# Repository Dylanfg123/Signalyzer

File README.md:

View this project on [CADLAB.io](https://cadlab.io/project/26944). 

# Signalyzer

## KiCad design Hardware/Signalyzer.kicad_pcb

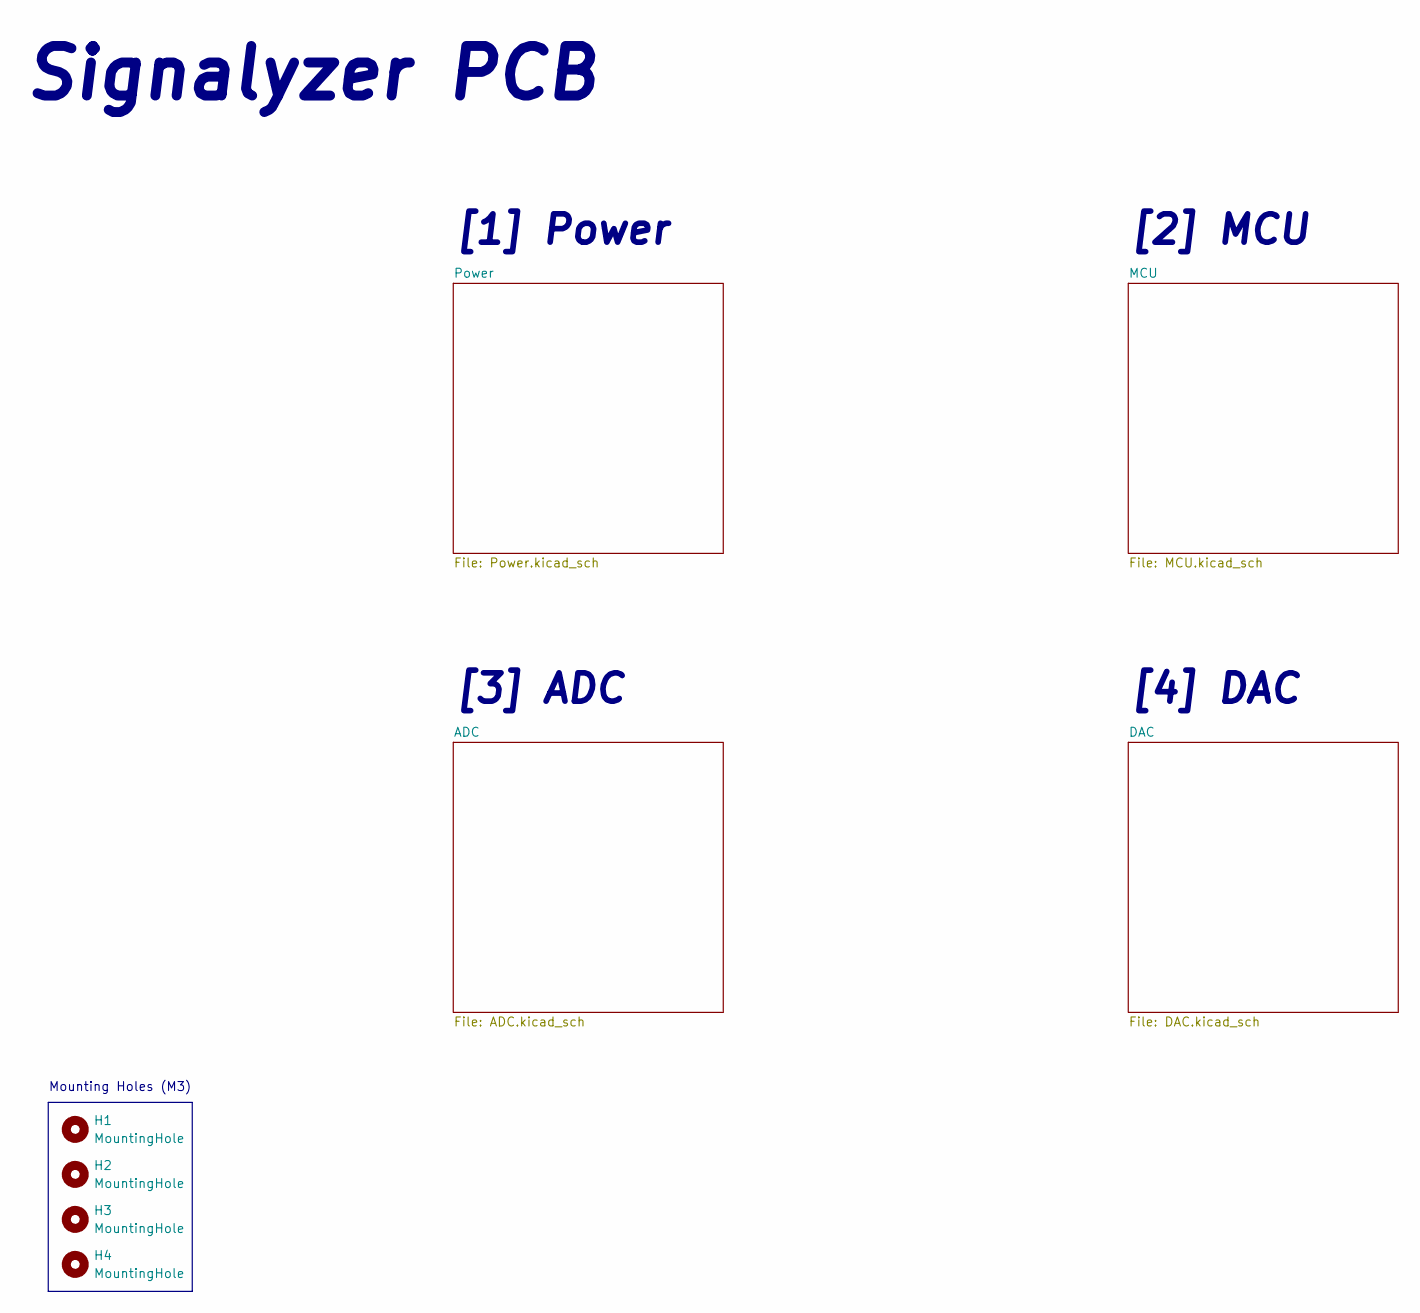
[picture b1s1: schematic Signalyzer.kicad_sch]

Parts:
H1, H2, H3, H4: MountingHole; MountingHole_3.2mm_M3

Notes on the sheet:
[2] MCU
Mounting Holes (M3)
[4] DAC
Signalyzer PCB
[3] ADC
[1] Power

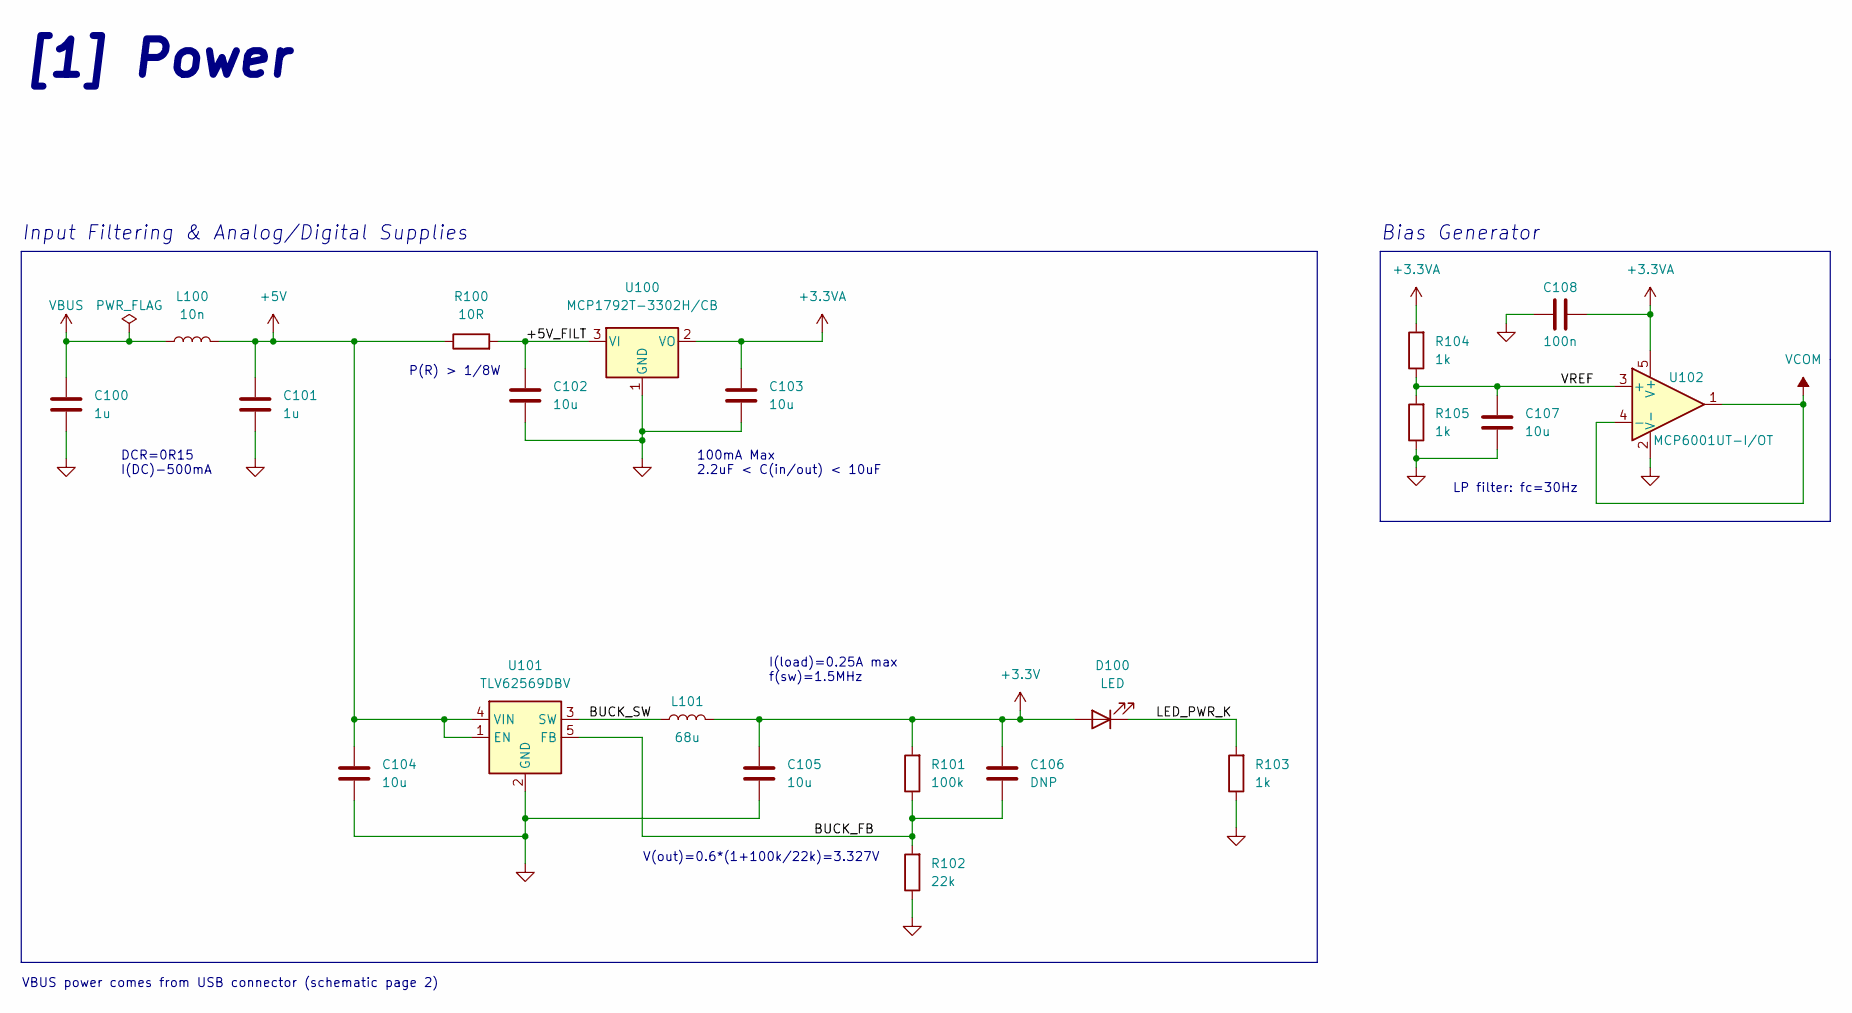
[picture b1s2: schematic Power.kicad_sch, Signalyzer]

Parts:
C100, C101: 1u; C_0603_1608Metric; Manufacturer Part Number CL10B105KA8VPJC; LCSC Part # C472462
C102, C103, C104, C105, C107: 10u; C_0603_1608Metric; Manufacturer Part Number GRM188R61C106KAALD; LCSC Part # C86275
C106: DNP; C_0402_1005Metric
C108: 100n; C_0402_1005Metric; Manufacturer Part Number CGA2B3X7R1V104KT0Y0F; LCSC Part # C343047
D100: LED; LED_0603_1608Metric; Manufacturer Part Number TJ-S1608SW6TDSLC2R2G-A5; LCSC Part # C601671
L100: 10n; L_0402_1005Metric; Manufacturer Part Number MHQ1005P10NJT000; LCSC Part # C445746
L101: 68u; L_1210_3225Metric; Manufacturer Part Number BCL322520RT-680M-D; LCSC Part # C3221319
R100: 10R; R_0805_2012Metric; Manufacturer Part Number RTAN0805BKE10R0; LCSC Part # C346749
R101: 100k; R_0402_1005Metric; Manufacturer Part Number ERA2AEB104X; LCSC Part # C445619
R102: 22k; R_0402_1005Metric; Manufacturer Part Number PTFR0402B22K0N9; LCSC Part # C2693021
R103, R104, R105: 1k; R_0402_1005Metric; Manufacturer Part Number ERA2AEB102X; LCSC Part # C445596
U100: MCP1792T-3302H/CB; SOT-23; Manufacturer Part Number MCP1792T-3302H/CB
U101: TLV62569DBV; SOT-23-5; Manufacturer Part Number TLV62569DBVR
U102: MCP6001UT-I/OT; SOT-23-5; Manufacturer Part Number MCP6001UT-I/OT

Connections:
+3.3VA: C103.1, C108.2, R104.2, U100.2 (VO), U102.5 (V+); also elsewhere on the board
+3V3: C105.1, C106.1, D100.2 (A), L101.2, R101.2; also elsewhere on the board
+5V: C101.1, C104.1, L100.2, R100.1, U101.1 (EN), U101.4 (VIN); also elsewhere on the board
/Power/+5V_FILT: C102.1, R100.2, U100.3 (VI)
/Power/BUCK_FB: C106.2, R101.1, R102.2, U101.5 (FB)
/Power/BUCK_SW: L101.1, U101.3 (SW)
/Power/LED_PWR_K: D100.1 (K), R103.2
/Power/VREF: C107.1, R104.1, R105.2, U102.3 (+)
GND: C100.2, C101.2, C102.2, C103.2, C104.2, C105.2, C107.2, C108.1, R102.1, R103.1, R105.1, U100.1 (GND), U101.2 (GND), U102.2 (V-); also elsewhere on the board
VBUS: C100.1, L100.1; also elsewhere on the board
VCOM: U102.1, U102.4 (-); also elsewhere on the board

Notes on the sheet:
100mA Max 2.2uF < C(in/out) < 10uF
VBUS power comes from USB connector (schematic page 2)
P(R) > 1/8W
V(out)=0.6*(1+100k/22k)=3.327V
LP filter: fc=30Hz
I(load)=0.25A max f(sw)=1.5MHz
DCR=0R15 I(DC)-500mA
Input Filtering & Analog/Digital Supplies
Bias Generator
[1] Power

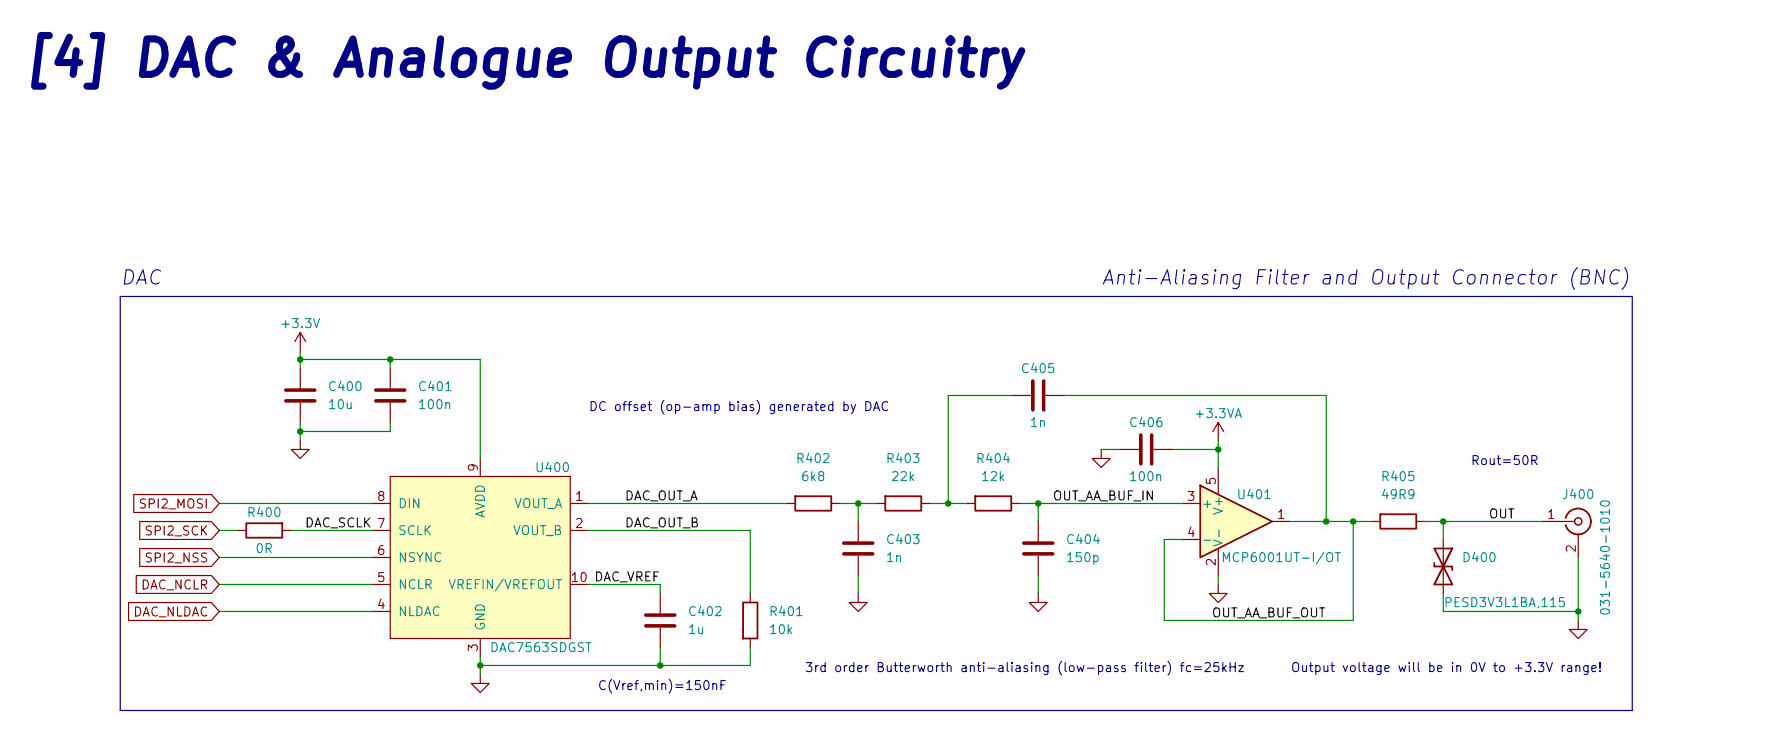
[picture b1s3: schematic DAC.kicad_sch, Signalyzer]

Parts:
C400: 10u; C_0603_1608Metric; Manufacturer Part Number GRM188R61C106KAALD; LCSC Part # C86275
C401, C406: 100n; C_0402_1005Metric; Manufacturer Part Number CGA2B3X7R1V104KT0Y0F; LCSC Part # C343047
C402: 1u; C_0603_1608Metric; Manufacturer Part Number CL10B105KA8VPJC; LCSC Part # C472462
C403, C405: 1n; C_0402_1005Metric; Manufacturer Part Number GRM1555C2A102GE01D; LCSC Part # C3010445
C404: 150p; C_0402_1005Metric; Manufacturer Part Number CC0402KRX7R9BB151; LCSC Part # C113789
D400: PESD3V3L1BA,115; D_SOD-323; Manufacturer Part Number PESD3V3L1BA,115; LCSC Part # C51450
J400: 031-5640-1010; BNC_Amphenol_B6252HB-NPP3G-50_Horizontal; Manufacturer Part Number 031-5640-1010
R400: 0R; R_0402_1005Metric; Manufacturer Part Number HCJ0402ZT0R00; LCSC Part # C346504
R401: 10k; R_0402_1005Metric; Manufacturer Part Number ERJPA2F1002X; LCSC Part # C427247
R402: 6k8; R_0402_1005Metric; Manufacturer Part Number ERA2VEB6801X; LCSC Part # C543679
R403: 22k; R_0402_1005Metric; Manufacturer Part Number PTFR0402B22K0N9; LCSC Part # C2693021
R404: 12k; R_0402_1005Metric; Manufacturer Part Number ERA2AEB123X; LCSC Part # C215763
R405: 49R9; R_0402_1005Metric; Manufacturer Part Number PTFR0402B49K9N9; LCSC Part # C2692755
U400: DAC7563SDGST; VSSOP-10; Manufacturer Part Number DAC7563SDGST
U401: MCP6001UT-I/OT; SOT-23-5; Manufacturer Part Number MCP6001UT-I/OT

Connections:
+3.3VA: C406.1, U401.5 (V+); also elsewhere on the board
+3V3: C400.1, C401.1, U400.9 (AVDD); also elsewhere on the board
/DAC/DAC_OUT_A: R402.2, U400.1 (VOUT_A)
/DAC/DAC_OUT_B: R401.1, U400.2 (VOUT_B)
/DAC/DAC_SCLK: R400.2, U400.7 (SCLK)
/DAC/DAC_VREF: C402.1, U400.10 (VREFIN/VREFOUT)
/DAC/OUT: D400.1 (A1), J400.1 (In), R405.1
/DAC/OUT_AA_BUF_IN: C404.1, R404.1, U401.3 (+)
/DAC/OUT_AA_BUF_OUT: C405.2, R405.2, U401.1, U401.4 (-)
DAC_NCLR: U400.5 (NCLR); also elsewhere on the board
DAC_NLDAC: U400.4 (NLDAC); also elsewhere on the board
GND: C400.2, C401.2, C402.2, C403.2, C404.2, C406.2, D400.2 (A2), J400.2 (Ext), R401.2, U400.3 (GND), U401.2 (V-); also elsewhere on the board
unnamed: C403.1, R402.1, R403.2
unnamed: C405.1, R403.1, R404.2
SPI2_MOSI: U400.8 (DIN); also elsewhere on the board
SPI2_NSS: U400.6 (NSYNC); also elsewhere on the board
SPI2_SCK: R400.1; also elsewhere on the board

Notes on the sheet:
Rout=50R
3rd order Butterworth anti-aliasing (low-pass filter) fc=25kHz
DAC
DC offset (op-amp bias) generated by DAC
Anti-Aliasing Filter and Output Connector (BNC)
C(Vref,min)=150nF
[4] DAC & Analogue Output Circuitry
Output voltage will be in 0V to +3.3V range!

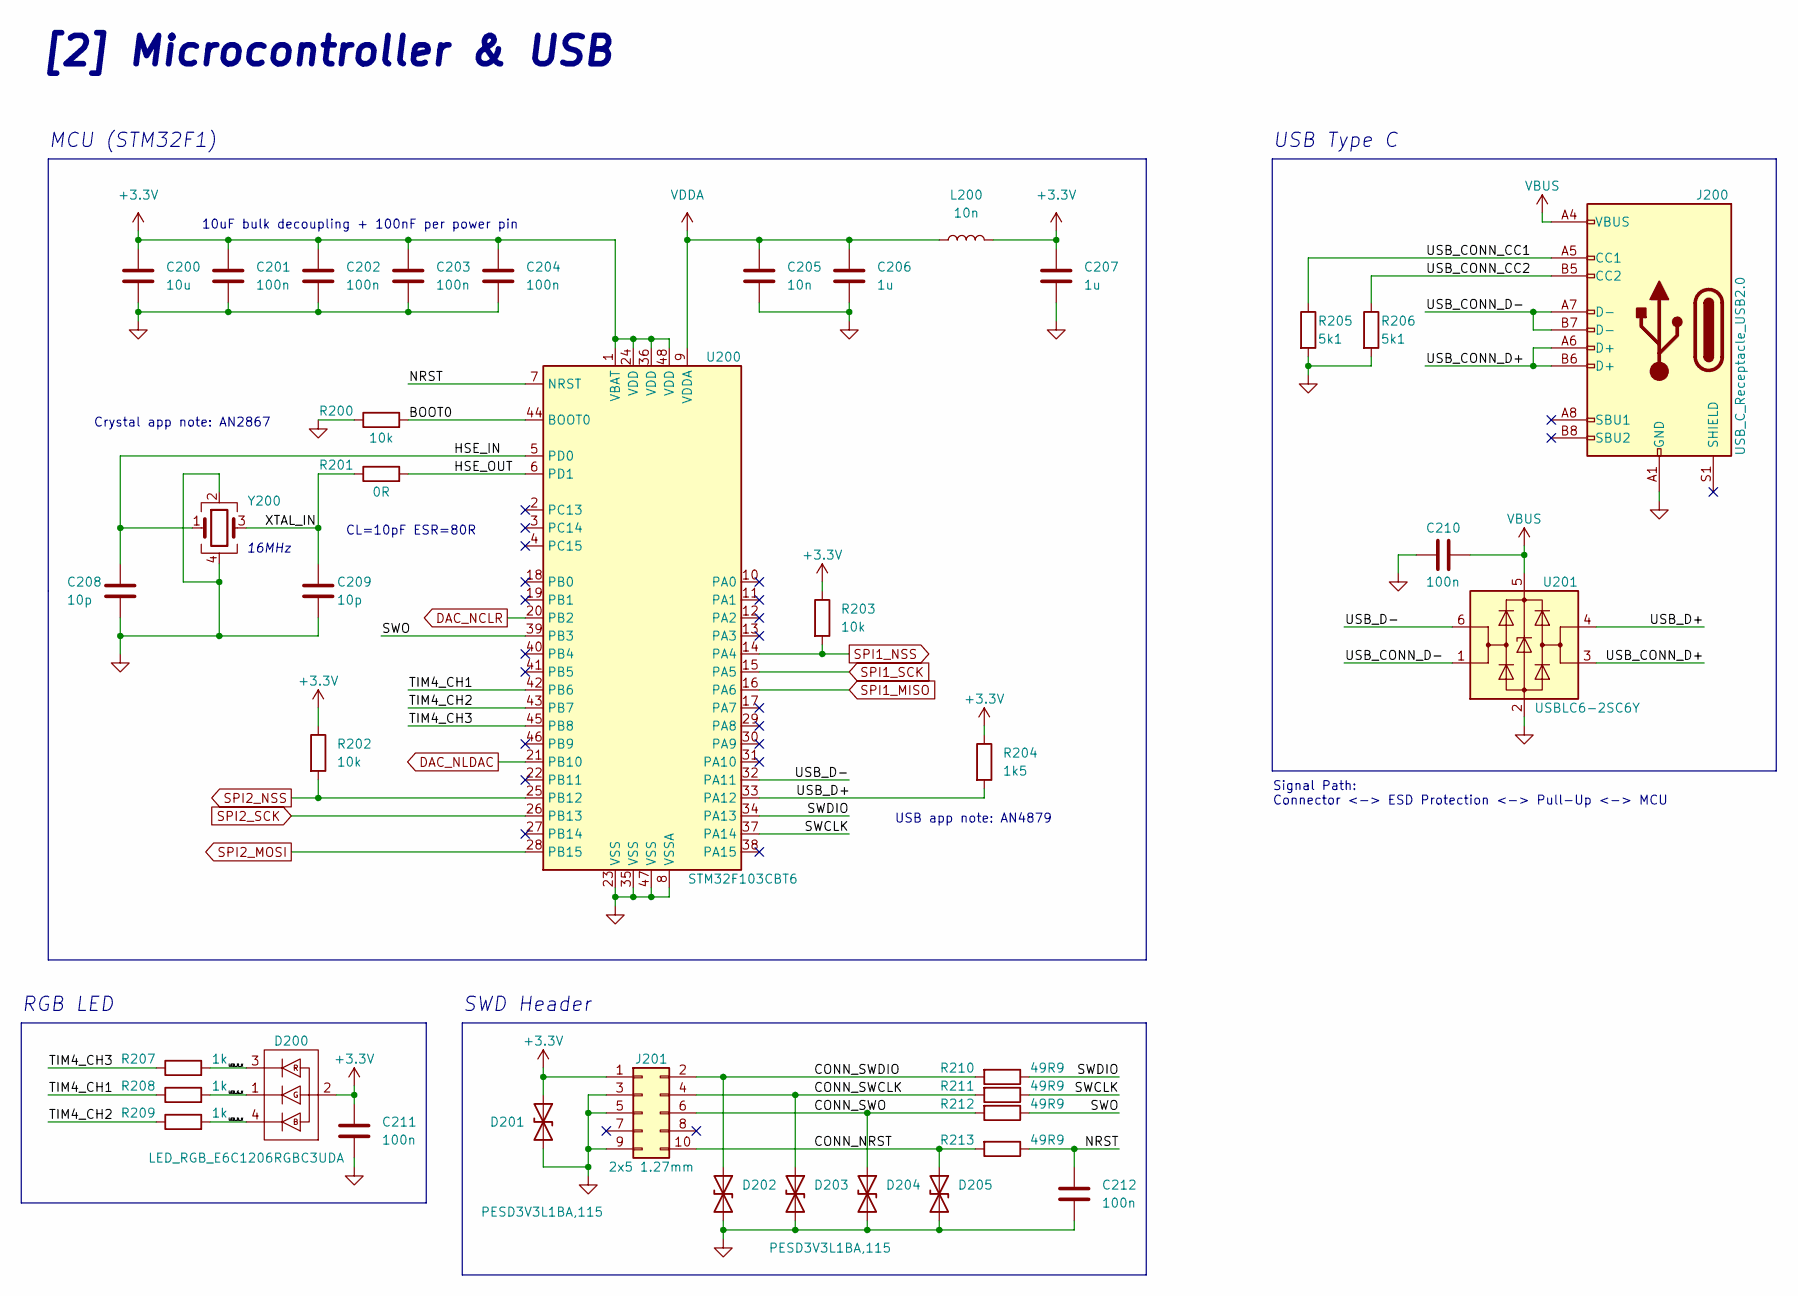
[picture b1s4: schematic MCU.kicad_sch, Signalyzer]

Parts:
C200: 10u; C_0603_1608Metric; Manufacturer Part Number GRM188R61C106KAALD; LCSC Part # C86275
C201, C202, C203, C204, C210, C211, C212: 100n; C_0402_1005Metric; Manufacturer Part Number CGA2B3X7R1V104KT0Y0F; LCSC Part # C343047
C205: 10n; C_0402_1005Metric; Manufacturer Part Number C0402C103K4RECAUTO; LCSC Part # C696351
C206, C207: 1u; C_0603_1608Metric; Manufacturer Part Number CL10B105KA8VPJC; LCSC Part # C472462
C208, C209: 10p; C_0402_1005Metric; Manufacturer Part Number 04023J100FBSTR; LCSC Part # C2154389
D200: LED_RGB_E6C1206RGBC3UDA; LED_Cree-PLCC4_2x2mm_CW; Manufacturer Part Number E6C1206RGBC3UDA; LCSC Part # C375571
D201, D202, D203, D204, D205: PESD3V3L1BA,115; D_SOD-323; Manufacturer Part Number PESD3V3L1BA,115; LCSC Part # C51450
J200: USB_C_Receptacle_USB2.0; USB_C_Receptacle_HRO_TYPE-C-31-M-12; Manufacturer Part Number TYPE-C-31-M-12; LCSC Part # C165948
J201: 2x5 1.27mm; PinHeader_2x05_P1.27mm_Vertical_SMD; Manufacturer Part Number DZ127S-22-10-55; LCSC Part # C5160761
L200: 10n; L_0402_1005Metric; Manufacturer Part Number MHQ1005P10NJT000; LCSC Part # C445746
R200, R202, R203: 10k; R_0402_1005Metric; Manufacturer Part Number ERJPA2F1002X; LCSC Part # C427247
R201: 0R; R_0402_1005Metric; Manufacturer Part Number HCJ0402ZT0R00; LCSC Part # C346504
R204: 1k5; R_0402_1005Metric; Manufacturer Part Number ERA2AEB152X; LCSC Part # C445600
R205, R206: 5k1; R_0402_1005Metric; Manufacturer Part Number ERA2AEB512X; LCSC Part # C490833
R207, R208, R209: 1k; R_0402_1005Metric; Manufacturer Part Number ERA2AEB102X; LCSC Part # C445596
R210, R211, R212, R213: 49R9; R_0402_1005Metric; Manufacturer Part Number PTFR0402B49K9N9; LCSC Part # C2692755
U200: STM32F103CBT6; LQFP-48_7x7mm_P0.5mm; Manufacturer Part Number STM32F103CBT6
U201: USBLC6-2SC6Y; SOT-23-6; Manufacturer Part Number USBLC6-2SC6Y
Y200: Crystal_GND24; Crystal_SMD_3225-4Pin_3.2x2.5mm; Manufacturer Part Number WTL3M01610; LCSC Part # C2857621

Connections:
+3V3: C200.1, C201.1, C202.1, C203.1, C204.1, C207.1, C211.1, D200.2, D201.1 (A1), J201.1, L200.2, R202.1, R203.1, R204.1, U200.1 (VBAT), U200.24 (VDD), U200.36 (VDD), U200.48 (VDD); also elsewhere on the board
/MCU/BOOT0: R200.2, U200.44 (BOOT0)
/MCU/CONN_NRST: D205.1 (A1), J201.10, R213.2
/MCU/CONN_SWCLK: D203.1 (A1), J201.4, R211.2
/MCU/CONN_SWDIO: D202.1 (A1), J201.2, R210.2
/MCU/CONN_SWO: D204.1 (A1), J201.6, R212.2
/MCU/HSE_IN: C208.1, U200.5 (PD0), Y200.1
/MCU/HSE_OUT: R201.2, U200.6 (PD1)
/MCU/LED_B_K: D200.4, R209.2
/MCU/LED_G_K: D200.1, R208.2
/MCU/LED_R_K: D200.3, R207.2
/MCU/NRST: C212.1, R213.1, U200.7 (NRST)
/MCU/SWCLK: R211.1, U200.37 (PA14)
/MCU/SWDIO: R210.1, U200.34 (PA13)
/MCU/SWO: R212.1, U200.39 (PB3)
/MCU/TIM4_CH1: R208.1, U200.42 (PB6)
/MCU/TIM4_CH2: R209.1, U200.43 (PB7)
/MCU/TIM4_CH3: R207.1, U200.45 (PB8)
/MCU/USB_CONN_CC1: J200.A5 (CC1), R205.1
/MCU/USB_CONN_CC2: J200.B5 (CC2), R206.1
/MCU/USB_CONN_D+: J200.A6 (D+), J200.B6 (D+), U201.3 (I/O2)
/MCU/USB_CONN_D-: J200.A7 (D-), J200.B7 (D-), U201.1 (I/O1)
/MCU/USB_D+: R204.2, U200.33 (PA12), U201.4 (I/O2)
/MCU/USB_D-: U200.32 (PA11), U201.6 (I/O1)
/MCU/XTAL_IN: C209.1, R201.1, Y200.3
DAC_NCLR: U200.20 (PB2); also elsewhere on the board
DAC_NLDAC: U200.21 (PB10); also elsewhere on the board
GND: C200.2, C201.2, C202.2, C203.2, C204.2, C205.2, C206.2, C207.2, C208.2, C209.2, C210.2, C211.2, C212.2, D201.2 (A2), D202.2 (A2), D203.2 (A2), D204.2 (A2), D205.2 (A2), J200.A1 (GND), J200.A12 (GND), J200.B1 (GND), J200.B12 (GND), J201.3, J201.5, J201.9, R200.1, R205.2, R206.2, U200.8 (VSSA), U200.23 (VSS), U200.35 (VSS), U200.47 (VSS), U201.2 (GND), Y200.2, Y200.4; also elsewhere on the board
SPI1_MISO: U200.16 (PA6); also elsewhere on the board
SPI1_NSS: R203.2, U200.14 (PA4); also elsewhere on the board
SPI1_SCK: U200.15 (PA5); also elsewhere on the board
SPI2_MOSI: U200.28 (PB15); also elsewhere on the board
SPI2_NSS: R202.2, U200.25 (PB12); also elsewhere on the board
SPI2_SCK: U200.26 (PB13); also elsewhere on the board
VBUS: C210.1, J200.A4 (VBUS), J200.A9 (VBUS), J200.B4 (VBUS), J200.B9 (VBUS), U201.5 (VBUS); also elsewhere on the board
VDDA: C205.1, C206.1, L200.1, U200.9 (VDDA)

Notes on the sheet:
10uF bulk decoupling + 100nF per power pin
SWD Header
CL=10pF ESR=80R
16MHz
USB app note: AN4879
Crystal app note: AN2867
[2] Microcontroller & USB
MCU (STM32F1)
USB Type C
RGB LED
Signal Path: Connector <-> ESD Protection <-> Pull-Up <-> MCU

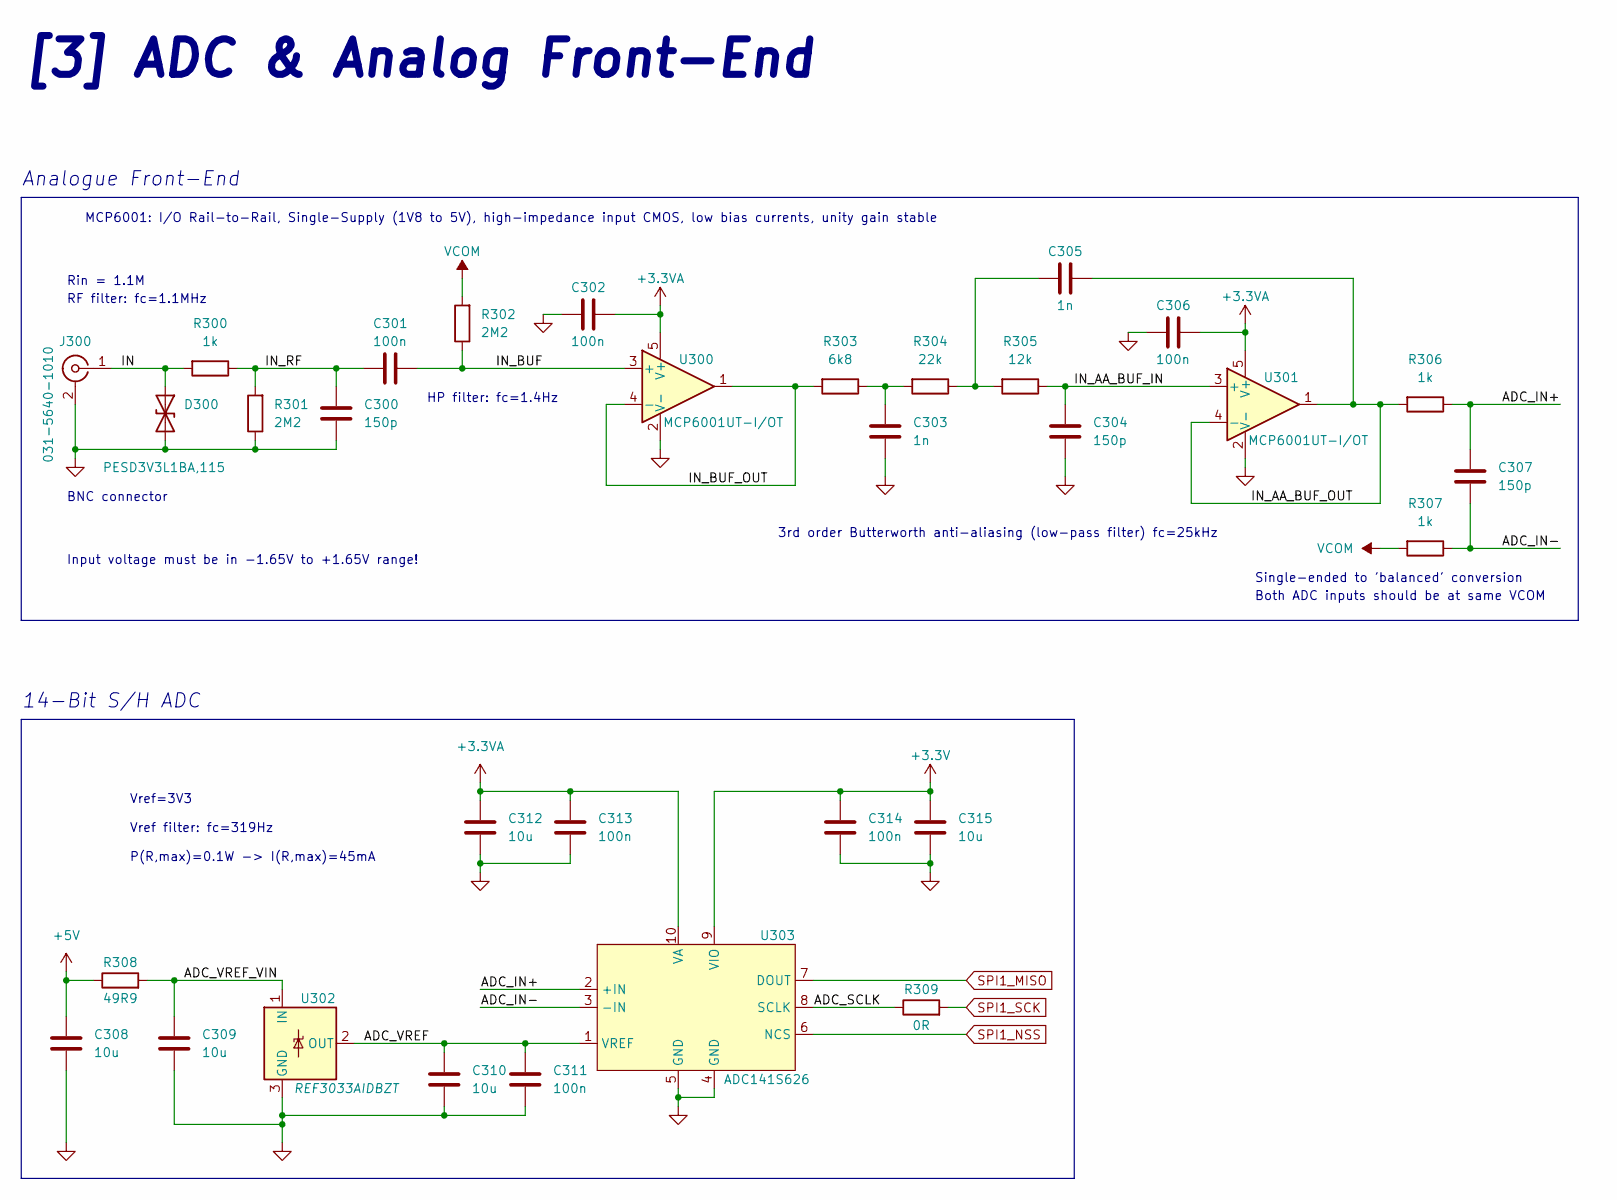
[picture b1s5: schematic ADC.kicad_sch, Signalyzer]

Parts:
C300, C304, C307: 150p; C_0402_1005Metric; Manufacturer Part Number CC0402KRX7R9BB151; LCSC Part # C113789
C301, C302, C306, C311, C313, C314: 100n; C_0402_1005Metric; Manufacturer Part Number CGA2B3X7R1V104KT0Y0F; LCSC Part # C343047
C303, C305: 1n; C_0402_1005Metric; Manufacturer Part Number GRM1555C2A102GE01D; LCSC Part # C3010445
C308, C309, C310, C312, C315: 10u; C_0603_1608Metric; Manufacturer Part Number GRM188R61C106KAALD; LCSC Part # C86275
D300: PESD3V3L1BA,115; D_SOD-323; Manufacturer Part Number PESD3V3L1BA,115; LCSC Part # C51450
J300: 031-5640-1010; BNC_Amphenol_B6252HB-NPP3G-50_Horizontal; Manufacturer Part Number 031-5640-1010
R300, R306, R307: 1k; R_0402_1005Metric; Manufacturer Part Number ERA2AEB102X; LCSC Part # C445596
R301, R302: 2M2; R_0402_1005Metric; Manufacturer Part Number CRCW04022M20FKED; LCSC Part # C482136
R303: 6k8; R_0402_1005Metric; Manufacturer Part Number ERA2VEB6801X; LCSC Part # C543679
R304: 22k; R_0402_1005Metric; Manufacturer Part Number PTFR0402B22K0N9; LCSC Part # C2693021
R305: 12k; R_0402_1005Metric; Manufacturer Part Number ERA2AEB123X; LCSC Part # C215763
R308: 49R9; R_0402_1005Metric; Manufacturer Part Number PTFR0402B49K9N9; LCSC Part # C2692755
R309: 0R; R_0402_1005Metric; Manufacturer Part Number HCJ0402ZT0R00; LCSC Part # C346504
U300, U301: MCP6001UT-I/OT; SOT-23-5; Manufacturer Part Number MCP6001UT-I/OT
U302: REF3033AIDBZT; SOT-23; Manufacturer Part Number REF3033AIDBZT
U303: ADC141S626; VSSOP-10; Manufacturer Part Number ADC141S626CIMM/NOPB

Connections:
+3.3VA: C302.1, C306.1, C312.1, C313.1, U300.5 (V+), U301.5 (V+), U303.10 (VA); also elsewhere on the board
+3V3: C314.1, C315.1, U303.9 (VIO); also elsewhere on the board
+5V: C308.1, R308.1; also elsewhere on the board
/ADC/ADC_IN+: C307.1, R306.1, U303.2 (+IN)
/ADC/ADC_IN-: C307.2, R307.1, U303.3 (-IN)
/ADC/ADC_SCLK: R309.1, U303.8 (SCLK)
/ADC/ADC_VREF: C310.1, C311.1, U302.2 (OUT), U303.1 (VREF)
/ADC/ADC_VREF_VIN: C309.1, R308.2, U302.1 (IN)
/ADC/IN: D300.1 (A1), J300.1 (In), R300.2
/ADC/IN_AA_BUF_IN: C304.1, R305.1, U301.3 (+)
/ADC/IN_AA_BUF_OUT: C305.2, R306.2, U301.1, U301.4 (-)
/ADC/IN_BUF: C301.1, R302.1, U300.3 (+)
/ADC/IN_BUF_OUT: R303.2, U300.1, U300.4 (-)
/ADC/IN_RF: C300.1, C301.2, R300.1, R301.2
GND: C300.2, C302.2, C303.2, C304.2, C306.2, C308.2, C309.2, C310.2, C311.2, C312.2, C313.2, C314.2, C315.2, D300.2 (A2), J300.2 (Ext), R301.1, U300.2 (V-), U301.2 (V-), U302.3 (GND), U303.4 (GND), U303.5 (GND); also elsewhere on the board
unnamed: C303.1, R303.1, R304.2
unnamed: C305.1, R304.1, R305.2
SPI1_MISO: U303.7 (DOUT); also elsewhere on the board
SPI1_NSS: U303.6 (NCS); also elsewhere on the board
SPI1_SCK: R309.2; also elsewhere on the board
VCOM: R302.2, R307.2; also elsewhere on the board

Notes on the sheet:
HP filter: fc=1.4Hz
Analogue Front-End
14-Bit S/H ADC
Rin = 1.1M
MCP6001: I/O Rail-to-Rail, Single-Supply (1V8 to 5V), high-impedance input CMOS, low bias currents, unity gain stable
Input voltage must be in -1.65V to +1.65V range!
3rd order Butterworth anti-aliasing (low-pass filter) fc=25kHz
BNC connector
Vref=3V3 Vref filter: fc=319Hz P(R,max)=0.1W -> I(R,max)=45mA
Both ADC inputs should be at same VCOM
RF filter: fc=1.1MHz
Single-ended to 'balanced' conversion
[3] ADC & Analog Front-End

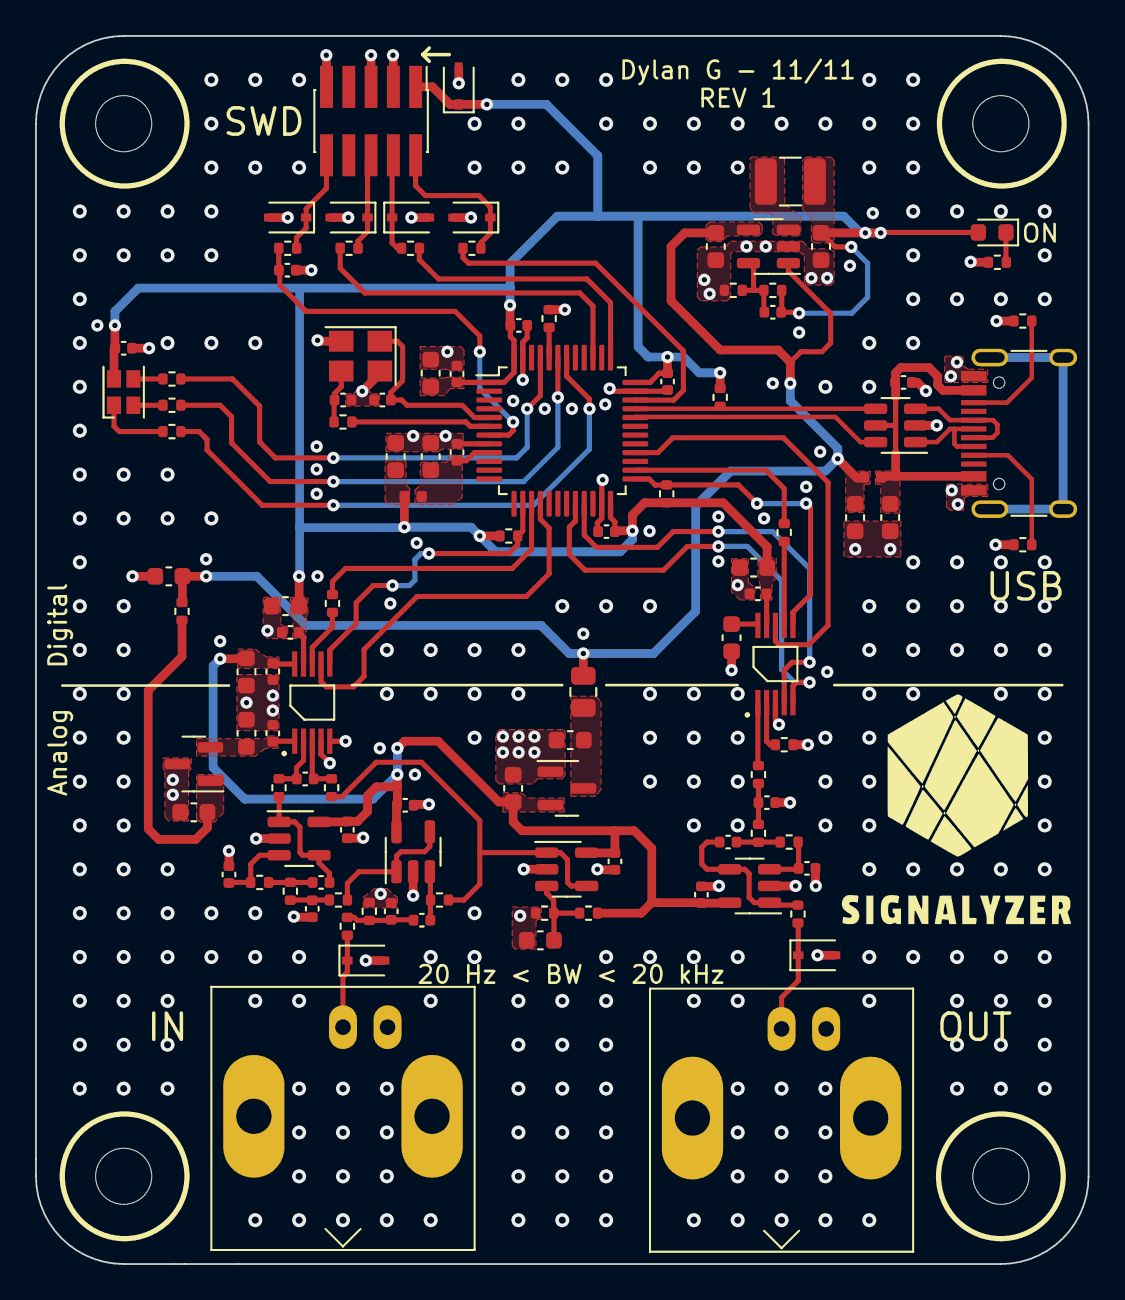
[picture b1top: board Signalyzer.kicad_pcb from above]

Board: 4 copper layers, 60.0 x 70.0 mm, 113 parts (0 on the bottom side), 66 nets.

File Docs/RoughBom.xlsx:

| Main
 | Part | Description | Qty | Price |  | Link | Alt Link
MCU | STM32F103CBT6 | ARM MCU, Motor Control, STM32 Family STM32F1 Series Microcontrollers, ARM Corte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 | 1 | 8.7799999999999994 | 11.07 | https://www.newark.com/stmicroelectronics/stm32f103cbt6/micr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 | https://www.arrow.com/en/products/stm32f103cbt6/stmicroelectronics
ADC | ADC141S626CIMM/NOPB | 14 Bit Analog to Digital Converter 1 Input 1 SAR 10-VSSOP | 1 | 11.71 |  | https://www.digikey.com/en/products/detail/ADC141S626CIMM-NO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
DAC | DAC7563TDGST | IC DAC 12BIT V-OUT 10VSSOP | 1 | 7.33 |  | https://www.digikey.com/en/products/detail/texas-instruments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
SW REG | TLV62569DBVR | Conv DC-DC 2.5V to 5.5V Synchronous Step Down Single-Out 0.6V to 5.5V 2A 5-Pin 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 | 1 | 0.89 |  | https://www.arrow.com/en/products/tlv62569dbvr/texas-instrum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
LDO | MCP1792T-3302H/CB | IC REG LIN 3.3V 100MA SOT23A-3 | 1 | 0.8 |  | https://www.digikey.com/en/products/detail/microchip-technol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
OPAMP | MCP6001UT-I/OT | IC OPAMP GP 1 CIRCUIT SOT23-5 |  | 0.32 |  | https://www.digikey.com/en/products/detail/microchip-technol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
ESD USB | USBLC6-2SC6Y | TVS DIODE 5.25VWM 17VC SOT23-6 | 1 | 1.07 |  | https://www.digikey.com/en/products/detail/stmicroelectronic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
TVS | PESD3V3L1BA,115 | TVS DIODE 3.3VWM 26VC SOD323 | 7 | 0.5 |  | https://www.digikey.com/en/products/detail/nexperia-usa-inc/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
 | Passives/Connectors
USB C | TYPE-C-31-M-12 | 5A 1 16 Female Type-C SMD USB Connectors ROHS | 1 | 1.1299999999999999 |  | https://www.lcsc.com/product-detail/USB-Type-C_Korean-Hropar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
RGB LED | E6C1206RGBC3UDA | RGB 1206 Light Emitting Diodes (LED) ROHS | 1 | 0.62 |  | https://www.lcsc.com/product-detail/Light-Emitting-Diodes-LE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
VREF | ref3033aidbzt | 3.3-V, 50-ppm/°C, 50-µA in 3-pin SOT-23 package series (bandgap) voltage refere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 | 1
BNC | 031-5640-1010 | Conn BNC 0Hz to 1GHz 50Ohm Solder RA Thru-Hole RCP Gold | 2 | 2.5299999999999998 |  | https://www.newark.com/amphenol-rf/031-5640-1010/rf-coaxial-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
crystal
 |  |  |  | 35.68 | 31.8
 |  |  |  | Spent so far: | 123.73

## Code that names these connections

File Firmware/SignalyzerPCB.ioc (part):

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Mcu.Name=STM32F103C(8-B)Tx
Mcu.Package=LQFP48
Mcu.UserName=STM32F103CBTx
PA11.Mode=Device
PA11.Signal=USB_DM
PA12.Mode=Device
PA12.Signal=USB_DP
PA13.Mode=Trace_Asynchronous_SW
PA13.Signal=SYS_JTMS-SWDIO
PA14.Mode=Trace_Asynchronous_SW
PA14.Signal=SYS_JTCK-SWCLK
PA4.Mode=NSS_Signal_Hard_Output
PA4.Signal=SPI1_NSS
PA5.Mode=RX_Only_Simplex_Unidirect_Master
PA5.Signal=SPI1_SCK
PA6.Mode=RX_Only_Simplex_Unidirect_Master
PA6.Signal=SPI1_MISO
PB12.Mode=NSS_Signal_Hard_Output
PB12.Signal=SPI2_NSS
PB13.Mode=TX_Only_Simplex_Unidirect_Master
PB13.Signal=SPI2_SCK
PB15.Mode=TX_Only_Simplex_Unidirect_Master
PB15.Signal=SPI2_MOSI
PB3.Mode=Trace_Asynchronous_SW
PB3.Signal=SYS_JTDO-TRACESWO
PB6.Signal=S_TIM4_CH1
PB7.Signal=S_TIM4_CH2
PB8.Signal=S_TIM4_CH3
PD0-OSC_IN.Mode=HSE-External-Oscillator
PD0-OSC_IN.Signal=RCC_OSC_IN
PD1-OSC_OUT.Mode=HSE-External-Oscillator
PD1-OSC_OUT.Signal=RCC_OSC_OUT
RCC.HSEDivPLL=RCC_HSE_PREDIV_DIV2
RCC.HSE_VALUE=16000000
RCC.SYSCLKFreq_VALUE=72000000
RCC.SYSCLKSource=RCC_SYSCLKSOURCE_PLLCLK
board=custom

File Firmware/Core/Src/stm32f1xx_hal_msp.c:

/* USER CODE BEGIN Header */
/**
  ******************************************************************************
  * @file         stm32f1xx_hal_msp.c
  * @brief        This file provides code for the MSP Initialization
  *               and de-Initialization codes.
  ******************************************************************************
  * @attention
  *
  * Copyright (c) 2022 STMicroelectronics.
  * All rights reserved.
  *
  * This software is licensed under terms that can be found in the LICENSE file
  * in the root directory of this software component.
  * If no LICENSE file comes with this software, it is provided AS-IS.
  *
  ******************************************************************************
  */
/* USER CODE END Header */

/* Includes ------------------------------------------------------------------*/
#include "main.h"
/* USER CODE BEGIN Includes */

/* USER CODE END Includes */

/* Private typedef -----------------------------------------------------------*/
/* USER CODE BEGIN TD */

/* USER CODE END TD */

/* Private define ------------------------------------------------------------*/
/* USER CODE BEGIN Define */

/* USER CODE END Define */

/* Private macro -------------------------------------------------------------*/
/* USER CODE BEGIN Macro */

/* USER CODE END Macro */

/* Private variables ---------------------------------------------------------*/
/* USER CODE BEGIN PV */

/* USER CODE END PV */

/* Private function prototypes -----------------------------------------------*/
/* USER CODE BEGIN PFP */

/* USER CODE END PFP */

/* External functions --------------------------------------------------------*/
/* USER CODE BEGIN ExternalFunctions */

/* USER CODE END ExternalFunctions */

/* USER CODE BEGIN 0 */

/* USER CODE END 0 */

void HAL_TIM_MspPostInit(TIM_HandleTypeDef *htim);
                    /**
  * Initializes the Global MSP.
  */
void HAL_MspInit(void)
{
  /* USER CODE BEGIN MspInit 0 */

  /* USER CODE END MspInit 0 */

  __HAL_RCC_AFIO_CLK_ENABLE();
  __HAL_RCC_PWR_CLK_ENABLE();

  /* System interrupt init*/

  /** NOJTAG: JTAG-DP Disabled and SW-DP Enabled
  */
  __HAL_AFIO_REMAP_SWJ_NOJTAG();

  /* USER CODE BEGIN MspInit 1 */

  /* USER CODE END MspInit 1 */
}

/**
* @brief SPI MSP Initialization
* This function configures the hardware resources used in this example
* @param hspi: SPI handle pointer
* @retval None
*/
void HAL_SPI_MspInit(SPI_HandleTypeDef* hspi)
{
  GPIO_InitTypeDef GPIO_InitStruct = {0};
  if(hspi->Instance==SPI1)
  {
  /* USER CODE BEGIN SPI1_MspInit 0 */

  /* USER CODE END SPI1_MspInit 0 */
    /* Peripheral clock enable */
    __HAL_RCC_SPI1_CLK_ENABLE();

    __HAL_RCC_GPIOA_CLK_ENABLE();
    /**SPI1 GPIO Configuration
    PA4     ------> SPI1_NSS
    PA5     ------> SPI1_SCK
    PA6     ------> SPI1_MISO
    */
    GPIO_InitStruct.Pin = GPIO_PIN_4|GPIO_PIN_5;
    GPIO_InitStruct.Mode = GPIO_MODE_AF_PP;
    GPIO_InitStruct.Speed = GPIO_SPEED_FREQ_HIGH;
    HAL_GPIO_Init(GPIOA, &GPIO_InitStruct);

    GPIO_InitStruct.Pin = GPIO_PIN_6;
    GPIO_InitStruct.Mode = GPIO_MODE_INPUT;
    GPIO_InitStruct.Pull = GPIO_NOPULL;
    HAL_GPIO_Init(GPIOA, &GPIO_InitStruct);

  /* USER CODE BEGIN SPI1_MspInit 1 */

  /* USER CODE END SPI1_MspInit 1 */
  }
  else if(hspi->Instance==SPI2)
  {
  /* USER CODE BEGIN SPI2_MspInit 0 */

  /* USER CODE END SPI2_MspInit 0 */
    /* Peripheral clock enable */
    __HAL_RCC_SPI2_CLK_ENABLE();

    __HAL_RCC_GPIOB_CLK_ENABLE();
    /**SPI2 GPIO Configuration
    PB12     ------> SPI2_NSS
    PB13     ------> SPI2_SCK
    PB15     ------> SPI2_MOSI
    */
    GPIO_InitStruct.Pin = GPIO_PIN_12|GPIO_PIN_13|GPIO_PIN_15;
    GPIO_InitStruct.Mode = GPIO_MODE_AF_PP;
    GPIO_InitStruct.Speed = GPIO_SPEED_FREQ_HIGH;
    HAL_GPIO_Init(GPIOB, &GPIO_InitStruct);

  /* USER CODE BEGIN SPI2_MspInit 1 */

  /* USER CODE END SPI2_MspInit 1 */
  }

}

/**
* @brief SPI MSP De-Initialization
* This function freeze the hardware resources used in this example
* @param hspi: SPI handle pointer
* @retval None
*/
void HAL_SPI_MspDeInit(SPI_HandleTypeDef* hspi)
{
  if(hspi->Instance==SPI1)
  {
  /* USER CODE BEGIN SPI1_MspDeInit 0 */

  /* USER CODE END SPI1_MspDeInit 0 */
    /* Peripheral clock disable */
    __HAL_RCC_SPI1_CLK_DISABLE();

    /**SPI1 GPIO Configuration
    PA4     ------> SPI1_NSS
    PA5     ------> SPI1_SCK
    PA6     ------> SPI1_MISO
    */
    HAL_GPIO_DeInit(GPIOA, GPIO_PIN_4|GPIO_PIN_5|GPIO_PIN_6);

  /* USER CODE BEGIN SPI1_MspDeInit 1 */

  /* USER CODE END SPI1_MspDeInit 1 */
  }
  else if(hspi->Instance==SPI2)
  {
  /* USER CODE BEGIN SPI2_MspDeInit 0 */

  /* USER CODE END SPI2_MspDeInit 0 */
    /* Peripheral clock disable */
    __HAL_RCC_SPI2_CLK_DISABLE();

    /**SPI2 GPIO Configuration
    PB12     ------> SPI2_NSS
    PB13     ------> SPI2_SCK
    PB15     ------> SPI2_MOSI
    */
    HAL_GPIO_DeInit(GPIOB, GPIO_PIN_12|GPIO_PIN_13|GPIO_PIN_15);

  /* USER CODE BEGIN SPI2_MspDeInit 1 */

  /* USER CODE END SPI2_MspDeInit 1 */
  }

}

/**
* @brief TIM_Base MSP Initialization
* This function configures the hardware resources used in this example
* @param htim_base: TIM_Base handle pointer
* @retval None
*/
void HAL_TIM_Base_MspInit(TIM_HandleTypeDef* htim_base)
{
  if(htim_base->Instance==TIM4)
  {
  /* USER CODE BEGIN TIM4_MspInit 0 */

  /* USER CODE END TIM4_MspInit 0 */
    /* Peripheral clock enable */
    __HAL_RCC_TIM4_CLK_ENABLE();
  /* USER CODE BEGIN TIM4_MspInit 1 */

  /* USER CODE END TIM4_MspInit 1 */
  }

}

void HAL_TIM_MspPostInit(TIM_HandleTypeDef* htim)
{
  GPIO_InitTypeDef GPIO_InitStruct = {0};
  if(htim->Instance==TIM4)
  {
  /* USER CODE BEGIN TIM4_MspPostInit 0 */

  /* USER CODE END TIM4_MspPostInit 0 */

    __HAL_RCC_GPIOB_CLK_ENABLE();
    /**TIM4 GPIO Configuration
    PB6     ------> TIM4_CH1
    PB7     ------> TIM4_CH2
    PB8     ------> TIM4_CH3
    */
    GPIO_InitStruct.Pin = GPIO_PIN_6|GPIO_PIN_7|GPIO_PIN_8;
    GPIO_InitStruct.Mode = GPIO_MODE_AF_PP;
    GPIO_InitStruct.Speed = GPIO_SPEED_FREQ_LOW;
    HAL_GPIO_Init(GPIOB, &GPIO_InitStruct);

  /* USER CODE BEGIN TIM4_MspPostInit 1 */

  /* USER CODE END TIM4_MspPostInit 1 */
  }

}
/**
* @brief TIM_Base MSP De-Initialization
* This function freeze the hardware resources used in this example
* @param htim_base: TIM_Base handle pointer
* @retval None
*/
void HAL_TIM_Base_MspDeInit(TIM_HandleTypeDef* htim_base)
{
  if(htim_base->Instance==TIM4)
  {
  /* USER CODE BEGIN TIM4_MspDeInit 0 */

  /* USER CODE END TIM4_MspDeInit 0 */
    /* Peripheral clock disable */
    __HAL_RCC_TIM4_CLK_DISABLE();
  /* USER CODE BEGIN TIM4_MspDeInit 1 */

  /* USER CODE END TIM4_MspDeInit 1 */
  }

}

/**
* @brief PCD MSP Initialization
* This function configures the hardware resources used in this example
* @param hpcd: PCD handle pointer
* @retval None
*/
void HAL_PCD_MspInit(PCD_HandleTypeDef* hpcd)
{
  if(hpcd->Instance==USB)
  {
  /* USER CODE BEGIN USB_MspInit 0 */

  /* USER CODE END USB_MspInit 0 */
    /* Peripheral clock enable */
    __HAL_RCC_USB_CLK_ENABLE();
  /* USER CODE BEGIN USB_MspInit 1 */

  /* USER CODE END USB_MspInit 1 */
  }

}

/**
* @brief PCD MSP De-Initialization
* This function freeze the hardware resources used in this example
* @param hpcd: PCD handle pointer
* @retval None
*/
void HAL_PCD_MspDeInit(PCD_HandleTypeDef* hpcd)
{
  if(hpcd->Instance==USB)
  {
  /* USER CODE BEGIN USB_MspDeInit 0 */

  /* USER CODE END USB_MspDeInit 0 */
    /* Peripheral clock disable */
    __HAL_RCC_USB_CLK_DISABLE();
  /* USER CODE BEGIN USB_MspDeInit 1 */

  /* USER CODE END USB_MspDeInit 1 */
  }

}

/* USER CODE BEGIN 1 */

/* USER CODE END 1 */

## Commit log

2023-05-13 Rev 1: Initial file commit before starting next rev
2023-05-13 Backlink to CADLAB.io has been added.
2023-05-13 updated gitignore to contain stmcubeIDE files
2023-05-13 Adding in FW files and split into HW and FW
